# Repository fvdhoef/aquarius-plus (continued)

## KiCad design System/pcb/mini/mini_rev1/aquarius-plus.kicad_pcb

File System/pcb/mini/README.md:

# Aquarius<sup>+</sup> Mini
A reduced-cost, small form factor version of the **Aquarius<sup>+</sup>**, designed as an entry point for 8-bit enthusiasts who want physical hardware.

## Introduction
The **Aquarius<sup>+</sup> Mini** retains all of the components relevant to enjoying the platform, but removes legacy hardware components that are more specific to collectors of original **Aquarius Computer** such as the cartridge and cassette ports. In November of 2024, the **Aquarius<sup>+</sup> Mini vZ** was introduced - "vZ" stands for Virtual Z80 - removing the physical Z80 chip and moving it into the FPGA along with the virtualized AY sound chips and the logic from the original PLA1 and PLA2 from the original **Aquarius Computer** architecture.

## PCB Revisions
 * **rev1** (aka Mini vZ) - Current release platform
   * Introduced: 22 NOV 2024
 * **rev0** - Z80-based hardware
   * Retired: 22 NOV 2024
   * Introduced: 24 FEB 2024

## Platform Comparison
| Feature | Aq<sup>+</sup> Mini | Aq<sup>+</sup> Standard |
| ---- | :----: | :----: |
| 512k RAM |  ✅  |  ✅  |
| 16k VRAM for Bitmaps, Tiles, and Sprites | ✅ | ✅ |
| 2 @ AY-3-8910 Sound Chips | In FPGA | In FPGA |
| Z80 CPU | In FPGA*, up to 28Mhz | Hardware, up to 7Mhz<br>In FPGA, up to 28Mhz |
| SD Card | ✅ | ✅ |
| Cassette Ports | :x: | ✅ |
| WiFi | ✅ | ✅ |
| Bluetooth LE | ✅ | ✅ |
| Soft loading of Cartridge and Cassette images | ✅ | ✅ |
| Expansion/Cartridge Port | :x: | ✅ |
| Wireless Game Controller Access | ✅ | ✅ |
| Wired Hand Controller Ports | :x: | ✅ |

*As of **rev1**, the **Aquarius<sup>+</sup> Mini** no longer relies on a physical Z80 CPU to function, moving it instead into the FPGA.

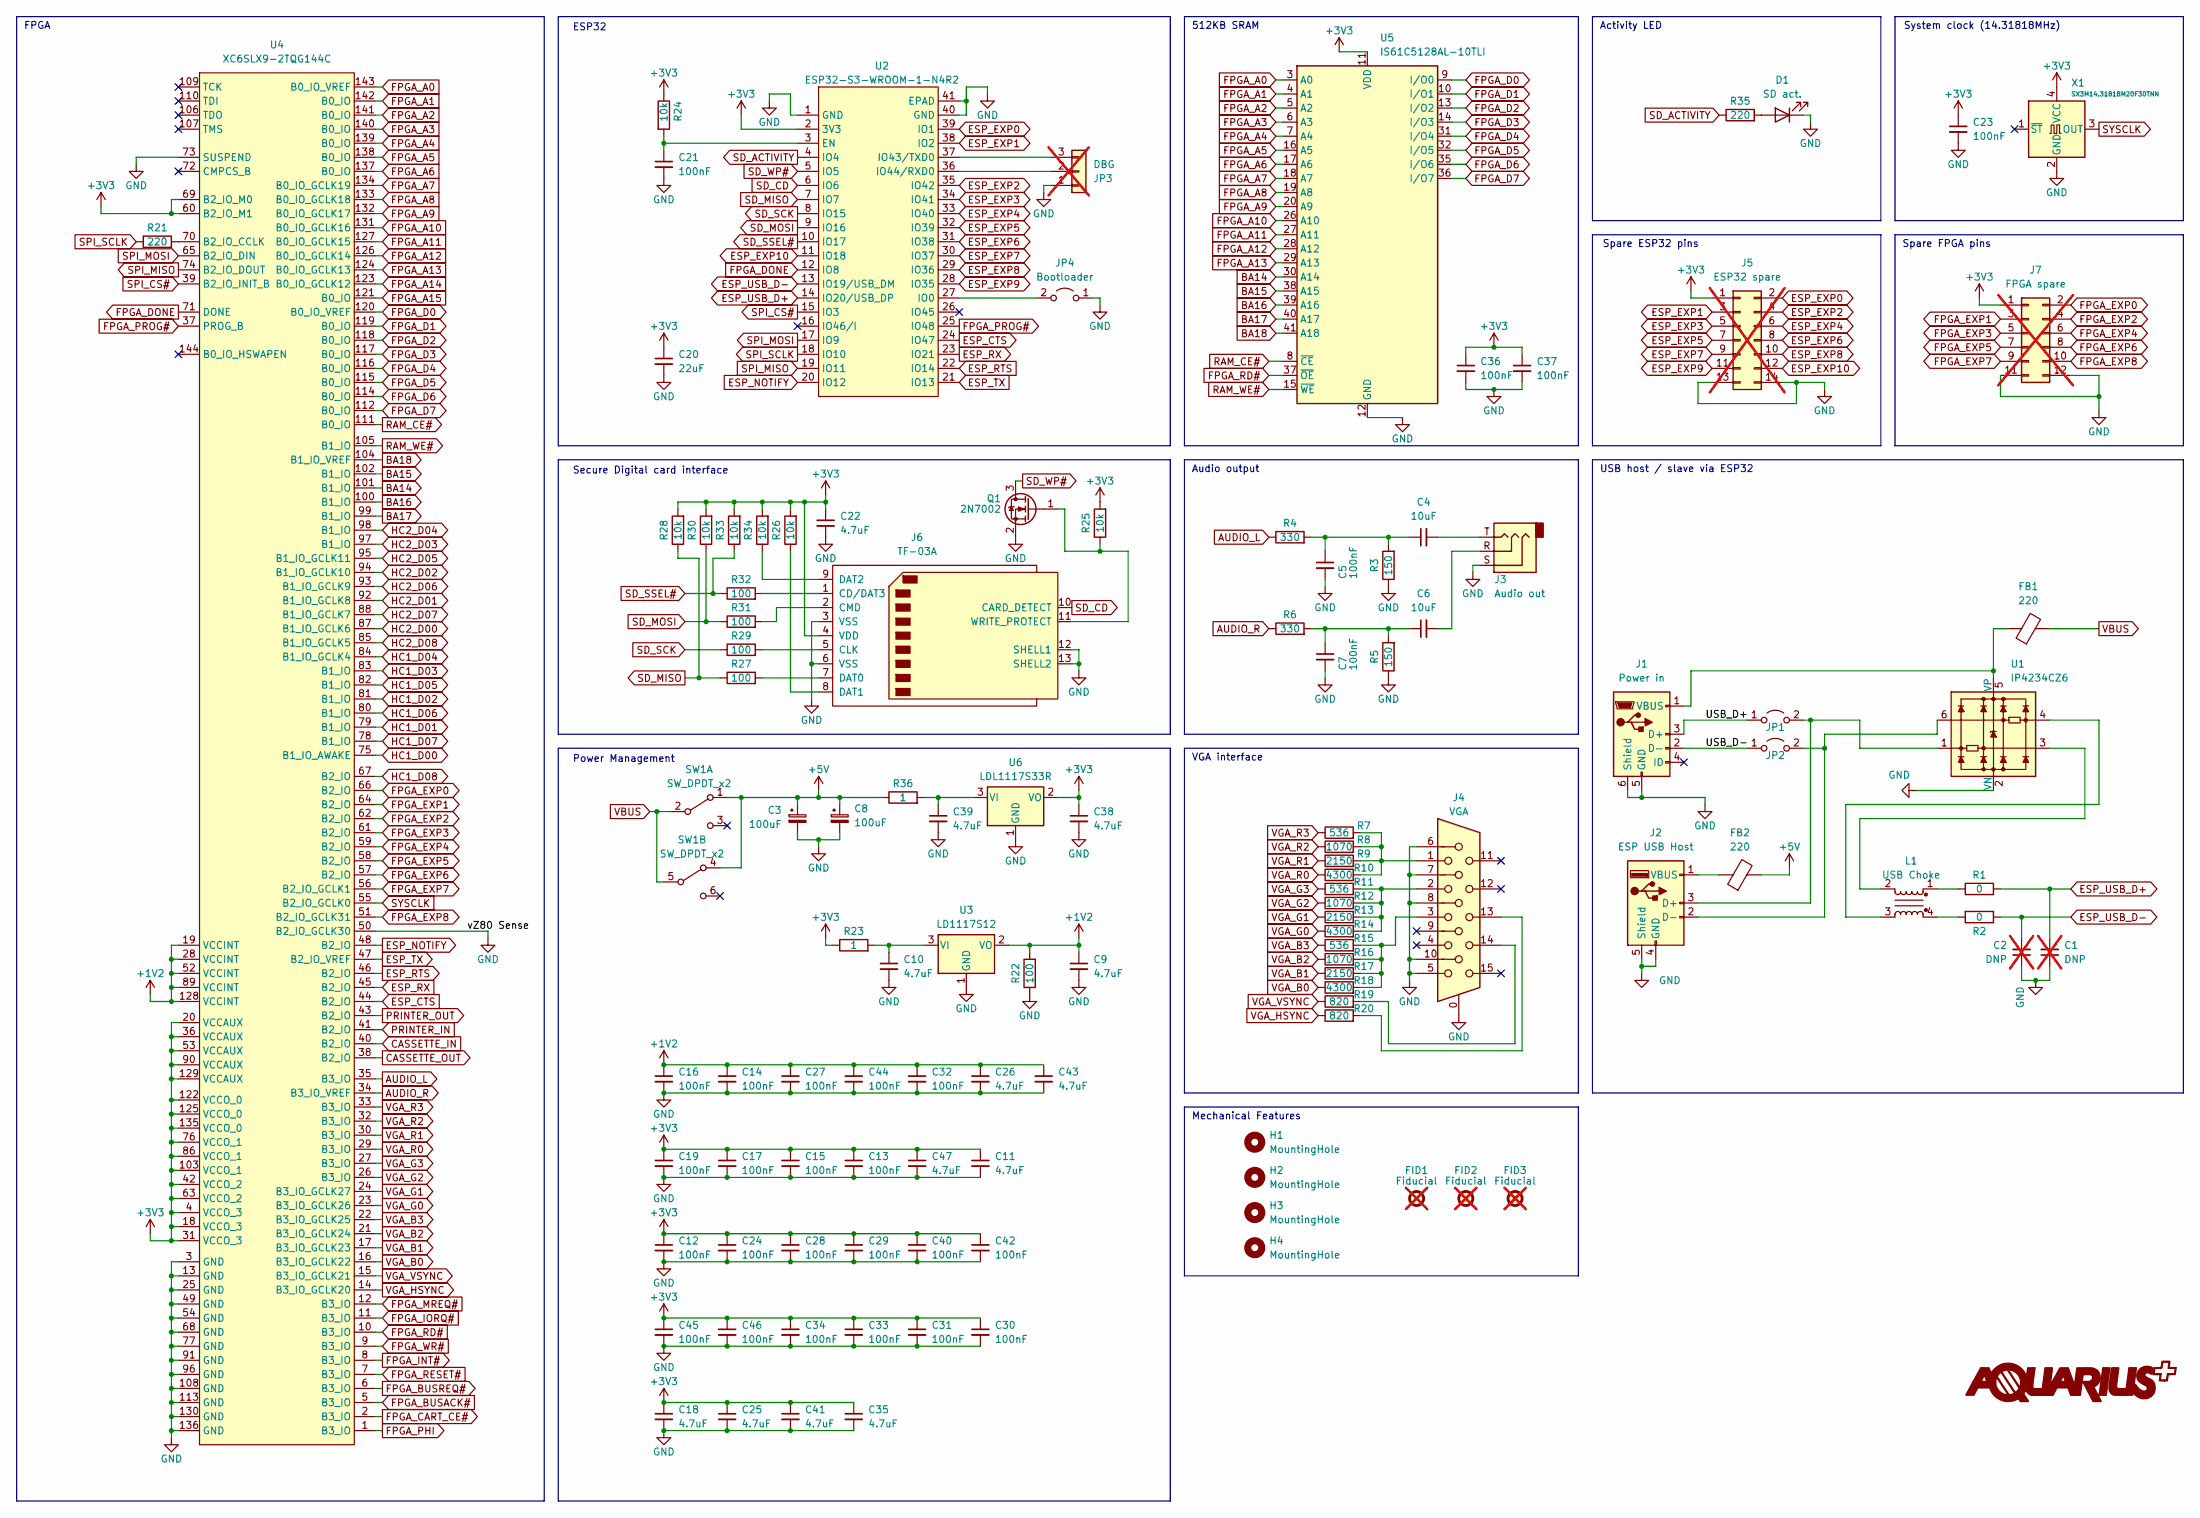
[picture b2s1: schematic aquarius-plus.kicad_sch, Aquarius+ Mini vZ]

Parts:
C1, C2: DNP; C_0603_1608Metric; not fitted
C3, C8: 100uF; CP_Elec_6.3x7.7
C4, C6: 10uF; C_0805_2012Metric
C5, C7, C12, C13, C14, C15, C16, C17, C19, C21, C23, C24, C27, C28, C29, C30, C31, C32, C33, C34, C36, C37, C40, C42, C44, C45, C46: 100nF; C_0603_1608Metric
C9, C10, C11, C18, C22, C25, C26, C35, C38, C39, C41, C43, C47: 4.7uF; C_0603_1608Metric
C20: 22uF; C_1206_3216Metric
D1: SD act.; LED_D3.0mm_Horizontal_O1.27mm_Z2.0mm
FB1, FB2: 220; L_0603_1608Metric
FID1, FID2, FID3: Fiducial; Fiducial_1mm_Mask2mm; not fitted
H1, H2, H3, H4: MountingHole; MountingHole_3.2mm_M3
J1: Power in; AMPHENOL_10118194-0001LF
J2: ESP USB Host; USB_A_Molex_67643_Horizontal
J3: Audio out; C2939180
J4: VGA; ICD15S13E4GV00LF
J5: ESP32 spare; PinHeader_2x07_P2.54mm_Vertical; not fitted
J6: TF-03A
J7: FPGA spare; PinHeader_2x06_P2.54mm_Vertical; not fitted
JP1, JP2: USB; PinHeader_1x02_P2.54mm_Vertical
JP3: DBG; PinHeader_1x03_P2.54mm_Vertical; not fitted
JP4: Bootloader; PinHeader_1x02_P2.54mm_Vertical
L1: USB Choke; WE-CNSW_08058
Q1: 2N7002; SOT-23
R1, R2: 0; R_0603_1608Metric
R3, R5: 150; R_0603_1608Metric
R4, R6: 330; R_0603_1608Metric
R7, R11, R15: 536; R_0603_1608Metric
R8, R12, R16: 1070; R_0603_1608Metric
R9, R13, R17: 2150; R_0603_1608Metric
R10, R14, R18: 4300; R_0603_1608Metric
R19, R20: 820; R_0603_1608Metric
R21, R35: 220; R_0603_1608Metric
R22, R27, R29, R31, R32: 100; R_0603_1608Metric
R23, R36: 1; R_0603_1608Metric
R24, R25, R26, R28, R30, R33, R34: 10k; R_0603_1608Metric
SW1: SW_DPDT_x2; SW_E-Switch_EG2219_DPDT_Angled
U1: IP4234CZ6; TSOT-23-6
U2: ESP32-S3-WROOM-1-N4R2; ESP32-S2-SOLO-N4R2
U3: LD1117S12; SOT-223-3_TabPin2
U4: XC6SLX9-2TQG144C; TQFP-144_20x20mm_P0.5mm
U5: IS61C5128AL-10TLI; TSOP-II-44_10.16x18.41mm_P0.8mm
U6: LDL1117S33R; SOT-223-3_TabPin2
X1: SX3M14.31818M20F30TNN; Oscillator_SMD_SeikoEpson_SG8002CE-4Pin_3.2x2.5mm

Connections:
+1V2: C9.1, C14.1, C16.1, C26.1, C27.1, C32.1, C43.1, C44.1, R22.2, U3.2 (VO), U4.19 (VCCINT), U4.28 (VCCINT), U4.52 (VCCINT), U4.89 (VCCINT), U4.128 (VCCINT)
+3V3: C11.1, C12.1, C13.1, C15.1, C17.1, C18.1, C19.1, C20.1, C22.1, C23.1, C24.1, C25.1, C28.1, C29.1, C30.1, C31.1, C33.1, C34.1, C35.1, C36.1, C37.1, C38.1, C40.1, C41.1, C42.1, C45.1, C46.1, C47.1, J5.1, J6.4 (VDD), J7.1, R23.1, R24.1, R25.2, R26.2, R28.2, R30.2, R33.2, R34.2, U2.2 (3V3), U4.4 (VCCO_3), U4.18 (VCCO_3), U4.20 (VCCAUX), U4.31 (VCCO_3), U4.36 (VCCAUX), U4.42 (VCCO_2), U4.53 (VCCAUX), U4.60 (B2_IO_M1), U4.63 (VCCO_2), U4.69 (B2_IO_M0), U4.76 (VCCO_1), U4.86 (VCCO_1), U4.90 (VCCAUX), U4.103 (VCCO_1), U4.122 (VCCO_0), U4.125 (VCCO_0), U4.129 (VCCAUX), U4.135 (VCCO_0), U5.11 (VDD), U5.33 (VDD), U6.2 (VO), X1.4 (VCC)
+5V: C3.1, C8.1, FB2.2, R36.1, SW1.1 (A), SW1.4 (A)
/USB_D+: J1.3 (D+), JP1.1 (A)
/USB_D-: J1.2 (D-), JP2.1 (A)
AUDIO_L: R4.1, U4.35 (B3_IO)
AUDIO_R: R6.1, U4.34 (B3_IO_VREF)
BA14: U4.101 (B1_IO), U5.30 (A14)
BA15: U4.102 (B1_IO), U5.38 (A15)
BA16: U4.100 (B1_IO), U5.39 (A16)
BA17: U4.99 (B1_IO), U5.40 (A17)
BA18: U4.104 (B1_IO_VREF), U5.41 (A18)
CASSETTE_IN: U4.40 (B2_IO)
CASSETTE_OUT: U4.38 (B2_IO)
ESP_CTS: U2.24 (IO47), U4.44 (B2_IO)
ESP_EXP0: J5.2, U2.39 (IO1)
ESP_EXP1: J5.3, U2.38 (IO2)
ESP_EXP2: J5.4, U2.35 (IO42)
ESP_EXP3: J5.5, U2.34 (IO41)
ESP_EXP4: J5.6, U2.33 (IO40)
ESP_EXP5: J5.7, U2.32 (IO39)
ESP_EXP6: J5.8, U2.31 (IO38)
ESP_EXP7: J5.9, U2.30 (IO37)
ESP_EXP8: J5.10, U2.29 (IO36)
ESP_EXP9: J5.11, U2.28 (IO35)
ESP_EXP10: J5.12, U2.11 (IO18)
ESP_NOTIFY: U2.20 (IO12), U4.48 (B2_IO)
ESP_RTS: U2.22 (IO14), U4.46 (B2_IO)
ESP_RX: U2.23 (IO21), U4.45 (B2_IO)
ESP_TX: U2.21 (IO13), U4.47 (B2_IO_VREF)
ESP_USB_D+: C1.2, R1.2, U2.14 (IO20/USB_DP)
ESP_USB_D-: C2.2, R2.1, U2.13 (IO19/USB_DM)
FPGA_A0: U4.143 (B0_IO_VREF), U5.3 (A0)
FPGA_A1: U4.142 (B0_IO), U5.4 (A1)
FPGA_A2: U4.141 (B0_IO), U5.5 (A2)
FPGA_A3: U4.140 (B0_IO), U5.6 (A3)
FPGA_A4: U4.139 (B0_IO), U5.7 (A4)
FPGA_A5: U4.138 (B0_IO), U5.16 (A5)
FPGA_A6: U4.137 (B0_IO), U5.17 (A6)
FPGA_A7: U4.134 (B0_IO_GCLK19), U5.18 (A7)
FPGA_A8: U4.133 (B0_IO_GCLK18), U5.19 (A8)
FPGA_A9: U4.132 (B0_IO_GCLK17), U5.20 (A9)
FPGA_A10: U4.131 (B0_IO_GCLK16), U5.26 (A10)
FPGA_A11: U4.127 (B0_IO_GCLK15), U5.27 (A11)
FPGA_A12: U4.126 (B0_IO_GCLK14), U5.28 (A12)
FPGA_A13: U4.124 (B0_IO_GCLK13), U5.29 (A13)
FPGA_A14: U4.123 (B0_IO_GCLK12)
FPGA_A15: U4.121 (B0_IO)
FPGA_BUSACK#: U4.5 (B3_IO)
FPGA_BUSREQ#: U4.6 (B3_IO)
FPGA_CART_CE#: U4.2 (B3_IO)
FPGA_D0: U4.120 (B0_IO_VREF), U5.9 (I/O0)
FPGA_D1: U4.119 (B0_IO), U5.10 (I/O1)
FPGA_D2: U4.118 (B0_IO), U5.13 (I/O2)
FPGA_D3: U4.117 (B0_IO), U5.14 (I/O3)
FPGA_D4: U4.116 (B0_IO), U5.31 (I/O4)
FPGA_D5: U4.115 (B0_IO), U5.32 (I/O5)
FPGA_D6: U4.114 (B0_IO), U5.35 (I/O6)
FPGA_D7: U4.112 (B0_IO), U5.36 (I/O7)
FPGA_DONE: U2.12 (IO8), U4.71 (DONE)
FPGA_EXP0: J7.2, U4.66 (B2_IO)
FPGA_EXP1: J7.3, U4.64 (B2_IO)
FPGA_EXP2: J7.4, U4.62 (B2_IO)
FPGA_EXP3: J7.5, U4.61 (B2_IO)
FPGA_EXP4: J7.6, U4.59 (B2_IO)
FPGA_EXP5: J7.7, U4.58 (B2_IO)
FPGA_EXP6: J7.8, U4.57 (B2_IO)
FPGA_EXP7: J7.9, U4.56 (B2_IO_GCLK1)
FPGA_EXP8: J7.10, U4.51 (B2_IO_GCLK31)
FPGA_INT#: U4.8 (B3_IO)
FPGA_IORQ#: U4.11 (B3_IO)
FPGA_MREQ#: U4.12 (B3_IO)
FPGA_PHI: U4.1 (B3_IO)
FPGA_PROG#: U2.25 (IO48), U4.37 (PROG_B)
FPGA_RD#: U4.10 (B3_IO), U5.37 (~OE)
FPGA_RESET#: U4.7 (B3_IO)
FPGA_WR#: U4.9 (B3_IO)
GND: C1.1, C2.1, C3.2, C5.2, C7.2, C8.2, C9.2, C10.2, C11.2, C12.2, C13.2, C14.2, C15.2, C16.2, C17.2, C18.2, C19.2, C20.2, C21.2, C22.2, C23.2, C24.2, C25.2, C26.2, C27.2, C28.2, C29.2, C30.2, C31.2, C32.2, C33.2, C34.2, C35.2, C36.2, C37.2, C38.2, C39.2, C40.2, C41.2, C42.2, C43.2, C44.2, C45.2, C46.2, C47.2, D1.1 (K), J1.5 (GND), J1.6 (Shield), J2.4 (GND), J2.5 (Shield), J3.S, J4.0, J4.5, J4.6, J4.7, J4.8, J4.10, J5.13, J5.14, J6.3 (VSS), J6.6 (VSS), J6.12 (SHELL1), J6.13 (SHELL2), J7.11, J7.12, JP3.1, JP4.1 (A), Q1.2 (S), R3.1, R5.1, R22.1, U1.2 (VN), U2.1 (GND), U2.40 (GND), U2.41 (EPAD), U3.1 (GND), U4.3 (GND), U4.13 (GND), U4.25 (GND), U4.49 (GND), U4.50 (B2_IO_GCLK30), U4.54 (GND), U4.68 (GND), U4.73 (SUSPEND), U4.77 (GND), U4.91 (GND), U4.96 (GND), U4.108 (GND), U4.113 (GND), U4.130 (GND), U4.136 (GND), U5.12 (GND), U5.34 (GND), U6.1 (GND), X1.2 (GND)
HC1_D00: U4.75 (B1_IO_AWAKE)
HC1_D01: U4.79 (B1_IO)
HC1_D02: U4.81 (B1_IO)
HC1_D03: U4.83 (B1_IO)
HC1_D04: U4.84 (B1_IO_GCLK4)
HC1_D05: U4.82 (B1_IO)
HC1_D06: U4.80 (B1_IO)
HC1_D07: U4.78 (B1_IO)
HC1_D08: U4.67 (B2_IO)
HC2_D00: U4.87 (B1_IO_GCLK6)
HC2_D01: U4.92 (B1_IO_GCLK8)
HC2_D02: U4.94 (B1_IO_GCLK10)
HC2_D03: U4.97 (B1_IO)
HC2_D04: U4.98 (B1_IO)
HC2_D05: U4.95 (B1_IO_GCLK11)
HC2_D06: U4.93 (B1_IO_GCLK9)
HC2_D07: U4.88 (B1_IO_GCLK7)
HC2_D08: U4.85 (B1_IO_GCLK5)
unnamed: C4.1, C5.1, R3.2, R4.2
unnamed: C4.2, J3.T
unnamed: C6.1, C7.1, R5.2, R6.2
unnamed: C6.2, J3.R
unnamed: D1.2 (A), R35.2
unnamed: FB1.1, J1.1 (VBUS), U1.5 (VP)
unnamed: J2.3 (D+), JP1.2 (B), U1.1
unnamed: J2.2 (D-), JP2.2 (B), U1.6
unnamed: FB2.1, J2.1 (VBUS)
unnamed: J4.1, R7.2, R8.2, R9.2, R10.2
unnamed: J4.2, R11.2, R12.2, R13.2, R14.2
unnamed: J4.3, R15.2, R16.2, R17.2, R18.2
unnamed: J4.13, R20.2
unnamed: J4.14, R19.2
unnamed: J6.1 (CD/DAT3), R32.2
unnamed: J6.5 (CLK), R29.2
unnamed: J6.2 (CMD), R31.2
unnamed: J6.7 (DAT0), R27.2
unnamed: J6.8 (DAT1), R26.1
unnamed: J6.9 (DAT2), R34.1
unnamed: J6.11 (WRITE_PROTECT), Q1.1 (G), R25.1
unnamed: JP3.2, U2.36 (IO44/RXD0)
unnamed: JP3.3, U2.37 (IO43/TXD0)
unnamed: JP4.2 (B), U2.27 (IO0)
unnamed: L1.1, R1.1
unnamed: L1.2, U1.3
unnamed: L1.3, U1.4
unnamed: L1.4, R2.2
unnamed: C21.1, R24.2, U2.3 (EN)
unnamed: C10.1, R23.2, U3.3 (VI)
unnamed: R21.2, U4.70 (B2_IO_CCLK)
unnamed: C39.1, R36.2, U6.3 (VI)
PRINTER_IN: U4.41 (B2_IO)
PRINTER_OUT: U4.43 (B2_IO)
RAM_CE#: U4.111 (B0_IO), U5.8 (~CE)
RAM_WE#: U4.105 (B1_IO), U5.15 (~WE)
SD_ACTIVITY: R35.1, U2.4 (IO4)
SD_CD: J6.10 (CARD_DETECT), U2.6 (IO6)
SD_MISO: R27.1, R28.1, U2.7 (IO7)
SD_MOSI: R30.1, R31.1, U2.9 (IO16)
SD_SCK: R29.1, U2.8 (IO15)
SD_SSEL#: R32.1, R33.1, U2.10 (IO17)
SD_WP#: Q1.3 (D), U2.5 (IO5)
SPI_CS#: U2.15 (IO3), U4.39 (B2_IO_INIT_B)
SPI_MISO: U2.19 (IO11), U4.74 (B2_IO_DOUT)
SPI_MOSI: U2.17 (IO9), U4.65 (B2_IO_DIN)
SPI_SCLK: R21.1, U2.18 (IO10)
SYSCLK: U4.55 (B2_IO_GCLK0), X1.3 (OUT)
VBUS: FB1.2, SW1.2 (B), SW1.5 (B)
VGA_B0: R18.1, U4.16 (B3_IO_GCLK22)
VGA_B1: R17.1, U4.17 (B3_IO_GCLK23)
VGA_B2: R16.1, U4.21 (B3_IO_GCLK24)
VGA_B3: R15.1, U4.22 (B3_IO_GCLK25)
VGA_G0: R14.1, U4.23 (B3_IO_GCLK26)
VGA_G1: R13.1, U4.24 (B3_IO_GCLK27)
VGA_G2: R12.1, U4.26 (B3_IO)
VGA_G3: R11.1, U4.27 (B3_IO)
VGA_HSYNC: R20.1, U4.14 (B3_IO_GCLK20)
VGA_R0: R10.1, U4.29 (B3_IO)
VGA_R1: R9.1, U4.30 (B3_IO)
VGA_R2: R8.1, U4.32 (B3_IO)
VGA_R3: R7.1, U4.33 (B3_IO)
VGA_VSYNC: R19.1, U4.15 (B3_IO_GCLK21)

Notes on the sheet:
System clock (14.31818MHz)
USB host / slave via ESP32
Audio output
Activity LED
Power Management
Spare FPGA pins
ESP32
512KB SRAM
FPGA
Spare ESP32 pins
VGA interface
Mechanical Features
Secure Digital card interface

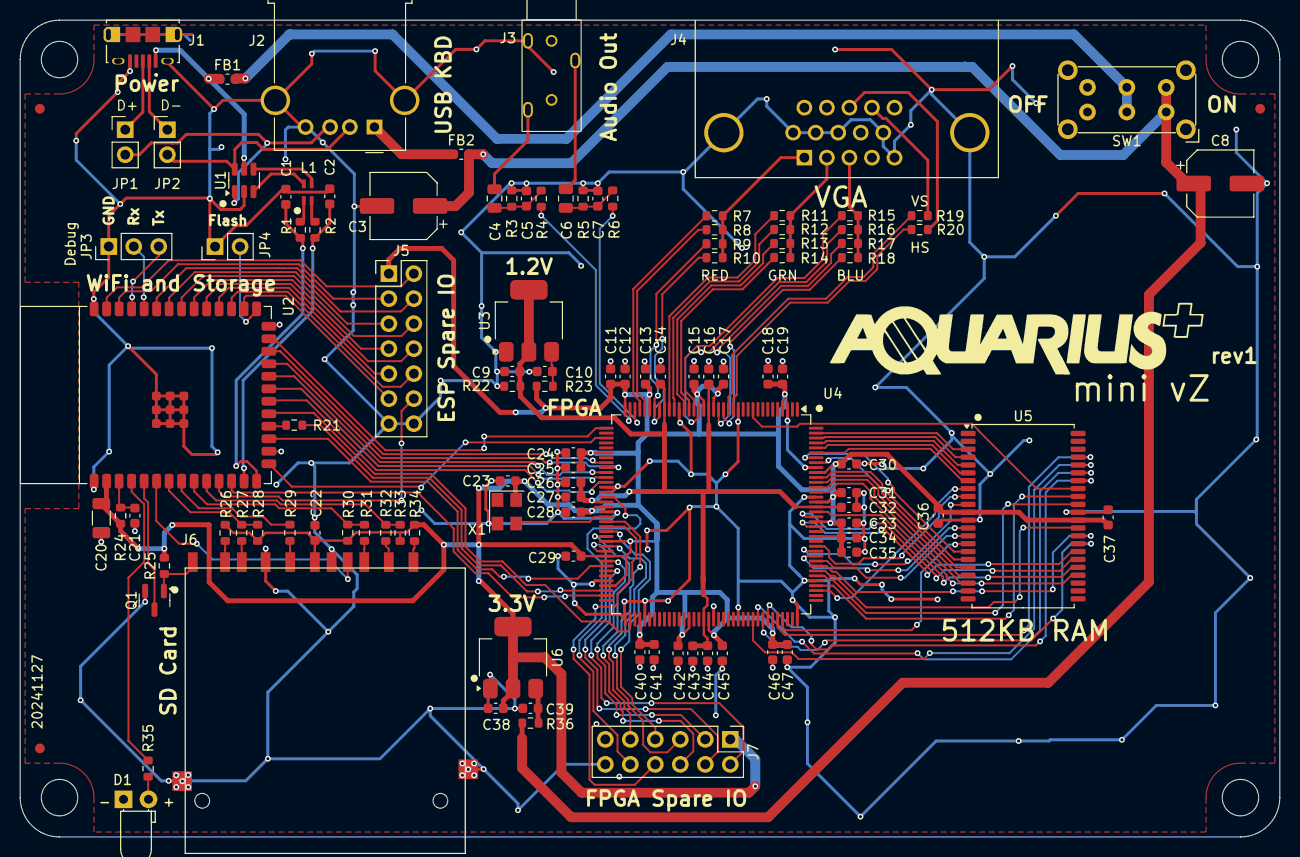
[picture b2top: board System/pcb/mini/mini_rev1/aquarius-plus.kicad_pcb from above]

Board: 2 copper layers, 128.0 x 83.0 mm, 114 parts (0 on the bottom side), 126 nets.

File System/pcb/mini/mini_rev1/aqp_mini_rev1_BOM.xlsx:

Designation | Designator | Footprint | JLCPCB Part #
4.7uF | C18,C38,C43,C11,C22,C39,C25,C47,C10,C41,C9,C35,C26 | C_0603_1608Metric | C19666
0 | R1,R2,R23,R36 | R_0603_1608Metric | C2784885
10k | R24,R33,R30,R26,R25,R28,R34 | R_0603_1608Metric | C881132
100nF | C36,C45,C7,C44,C37,C17,C24,C13,C33,C34,C40,C21,C31,C32,C12,C29,C42,C27,C5,C30,C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 | C_0603_1608Metric | C14663
Pin Header | JP1,JP2,JP4 | PinHeader_1x02_P2.54mm_Vertical | C2905434
4300 | R14,R18,R10 | R_0603_1608Metric | C23159
1070 | R16,R8,R12 | R_0603_1608Metric | C402876
IP4234CZ6 | U1 | SC-74-6_1.55x2.9mm_P0.95mm | C455086
LD1117S12 | U3 | SOT-223-3_TabPin2 | C155612
100 | R32,R22,R29,R31,R27 | R_0603_1608Metric | C22775
XC6SLX9-2TQG144C | U4 | TQFP-144_20x20mm_P0.5mm | C27408
2150 | R9,R13,R17 | R_0603_1608Metric | C273772
10uF | C6,C4 | C_0805_2012Metric | C15850
330 | R4,R6 | R_0603_1608Metric | C23138
220 @ 100mHz | FB1,FB2 | L_0603_1608Metric | C2661695
SW_DPDT_x2 | SW1 | SW_E-Switch_EG2219_DPDT_Angled | C3664594
820 | R20,R19 | R_0603_1608Metric | C23253
IS61C5128AL-10TLI | U5 | TSOP-II-44_10.16x18.41mm_P0.8mm | C40493
536 | R15,R7,R11 | R_0603_1608Metric | C227956
150 | R3,R5 | R_0603_1608Metric | C22808
Power in | J1 | AMPHENOL_10118194-0001LF | C132563
LDL1117S33R | U6 | SOT-223-3_TabPin2 | C435835
220 | R35,R21 | R_0603_1608Metric | C22962
TF-03A | J6 | TF-03A | C693842
VGA | J4 | ICD15S13E4GV00LF | C138387
ESP USB Host | J2 | USB_A_Molex_67643_Horizontal | C2798029
3.0mm Blue LED | D1 | LED_D3.0mm_Horizontal_O1.27mm_Z2.0mm | C330760
100uF | C3,C8 | CP_Elec_6.3x7.7 | C264047
SX3M14.31818M20F30TNN | X1 | Oscillator_SMD_SeikoEpson_SG8002CE-4Pin_3.2x2.5mm | C2901565
22uF | C20 | C_1206_3216Metric | C12891
Audio out | J3 | C2939180 | C2689690
ESP32-S3-WROOM-1-N4R2 | U2 | ESP32-S2-SOLO-N4R2 | C2913203
USB Choke | L1 | L_CommonMode_Wurth_WE-CNSW-1206 | C2649327
2N7002 | Q1 | SOT-23 | C8545
